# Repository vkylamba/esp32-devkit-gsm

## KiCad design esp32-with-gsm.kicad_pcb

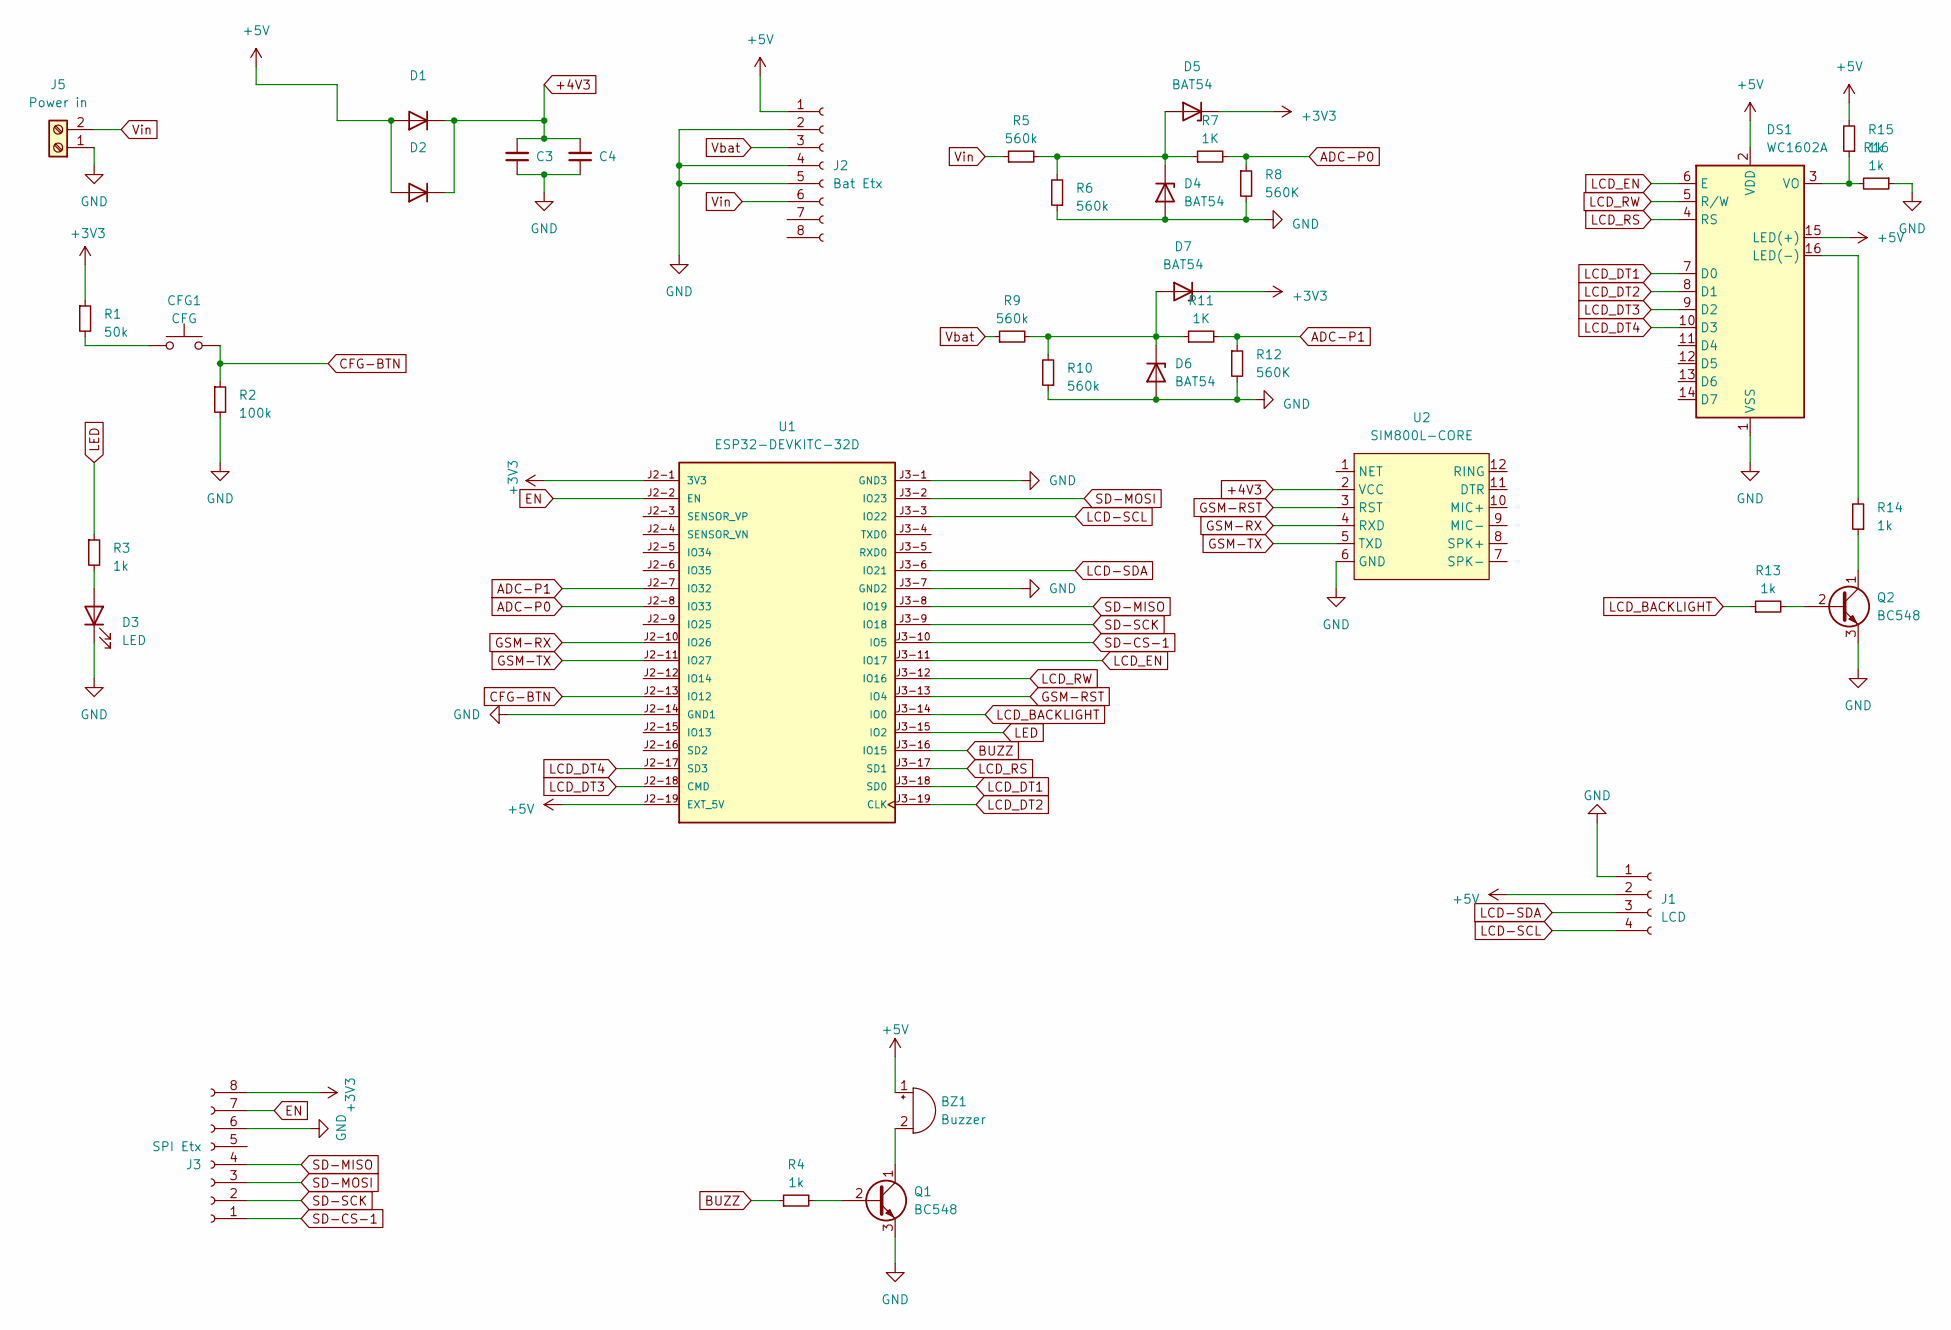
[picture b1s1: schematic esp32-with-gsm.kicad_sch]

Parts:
BZ1: Buzzer; Buzzer_12x9.5RM7.6
C3, C4: 470uF; C_Disc_D8.0mm_W2.5mm_P5.00mm
CFG1: CFG; PinHeader_1x02_P2.00mm_Vertical
D1, D2: 1N4007, SS14; D_0805_2012Metric
D3: LED; LED_D3.0mm_FlatTop
D4, D5, D6, D7: BAT54; D_0805_2012Metric
DS1: WC1602A
J1: LCD; PinHeader_1x04_P2.54mm_Vertical
J2: Bat Etx; PinHeader_1x08_P2.54mm_Vertical
J3: SPI Etx; PinHeader_1x08_P2.54mm_Vertical
J5: Power in; TerminalBlock_Altech_AK300-2_P5.00mm
Q1, Q2: BC548; TO-92_Inline
R1: 50k; R_0805_2012Metric
R2: 100k; R_0805_2012Metric
R3, R4, R13, R14, R15, R16: 1k; R_0805_2012Metric
R5, R6, R9, R10: 560k; R_0805_2012Metric
R7, R11: 1K; R_0805_2012Metric
R8, R12: 560K; R_0805_2012Metric
U1: ESP32-DEVKITC-32D; MODULE_ESP32-DEVKITC-32D; PARTREV V4
U2: SIM800L-CORE

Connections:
+3V3: D5.1 (K), D7.1 (K), J3.8, R1.1, U1.J2-1 (3V3)
+4V3: C3.2, C4.2, D1.1 (K), D2.1 (K), U2.2 (VCC)
+5V: BZ1.1 (+), D1.2 (A), D2.2 (A), DS1.2 (VDD), DS1.15 (LED(+)), J1.2, J2.1, R15.2, U1.J2-19 (EXT_5V)
ADC-P0: R7.2, R8.1, U1.J2-8 (IO33)
ADC-P1: R11.2, R12.1, U1.J2-7 (IO32)
BUZZ: R4.1, U1.J3-16 (IO15)
CFG-BTN: CFG1.2, R2.1, U1.J2-13 (IO12)
EN: J3.7, U1.J2-2 (EN)
GND: C3.1, C4.1, D3.1 (K), D4.2 (A), D6.2 (A), DS1.1 (VSS), J1.1, J2.2, J2.4, J2.5, J3.6, J5.1, Q1.3 (E), Q2.3 (E), R2.2, R6.1, R8.2, R10.1, R12.2, R16.1, U1.J2-14 (GND1), U1.J3-1 (GND3), U1.J3-7 (GND2), U2.6 (GND)
GSM-RST: U1.J3-13 (IO4), U2.3 (RST)
GSM-RX: U1.J2-10 (IO26), U2.4 (RXD)
GSM-TX: U1.J2-11 (IO27), U2.5 (TXD)
LCD-SCL: J1.4, U1.J3-3 (IO22)
LCD-SDA: J1.3, U1.J3-6 (IO21)
LCD_BACKLIGHT: R13.1, U1.J3-14 (IO0)
LCD_DT1: DS1.7 (D0), U1.J3-18 (SD0)
LCD_DT2: DS1.8 (D1), U1.J3-19 (CLK)
LCD_DT3: DS1.9 (D2), U1.J2-18 (CMD)
LCD_DT4: DS1.10 (D3), U1.J2-17 (SD3)
LCD_EN: DS1.6 (E), U1.J3-11 (IO17)
LCD_RS: DS1.4 (RS), U1.J3-17 (SD1)
LCD_RW: DS1.5 (R/W), U1.J3-12 (IO16)
LED: R3.1, U1.J3-15 (IO2)
unnamed: BZ1.2 (-), Q1.1 (C)
unnamed: CFG1.1, R1.2
unnamed: D3.2 (A), R3.2
unnamed: D4.1 (K), D5.2 (A), R5.2, R6.2, R7.1
unnamed: D6.1 (K), D7.2 (A), R9.2, R10.2, R11.1
unnamed: DS1.16 (LED(-)), R14.2
unnamed: DS1.3 (VO), R15.1, R16.2
unnamed: Q1.2 (B), R4.2
unnamed: Q2.2 (B), R13.2
unnamed: Q2.1 (C), R14.1
SD-CS-1: J3.1, U1.J3-10 (IO5)
SD-MISO: J3.4, U1.J3-8 (IO19)
SD-MOSI: J3.3, U1.J3-2 (IO23)
SD-SCK: J3.2, U1.J3-9 (IO18)
Vbat: J2.3, R9.1
Vin: J2.6, J5.2, R5.1

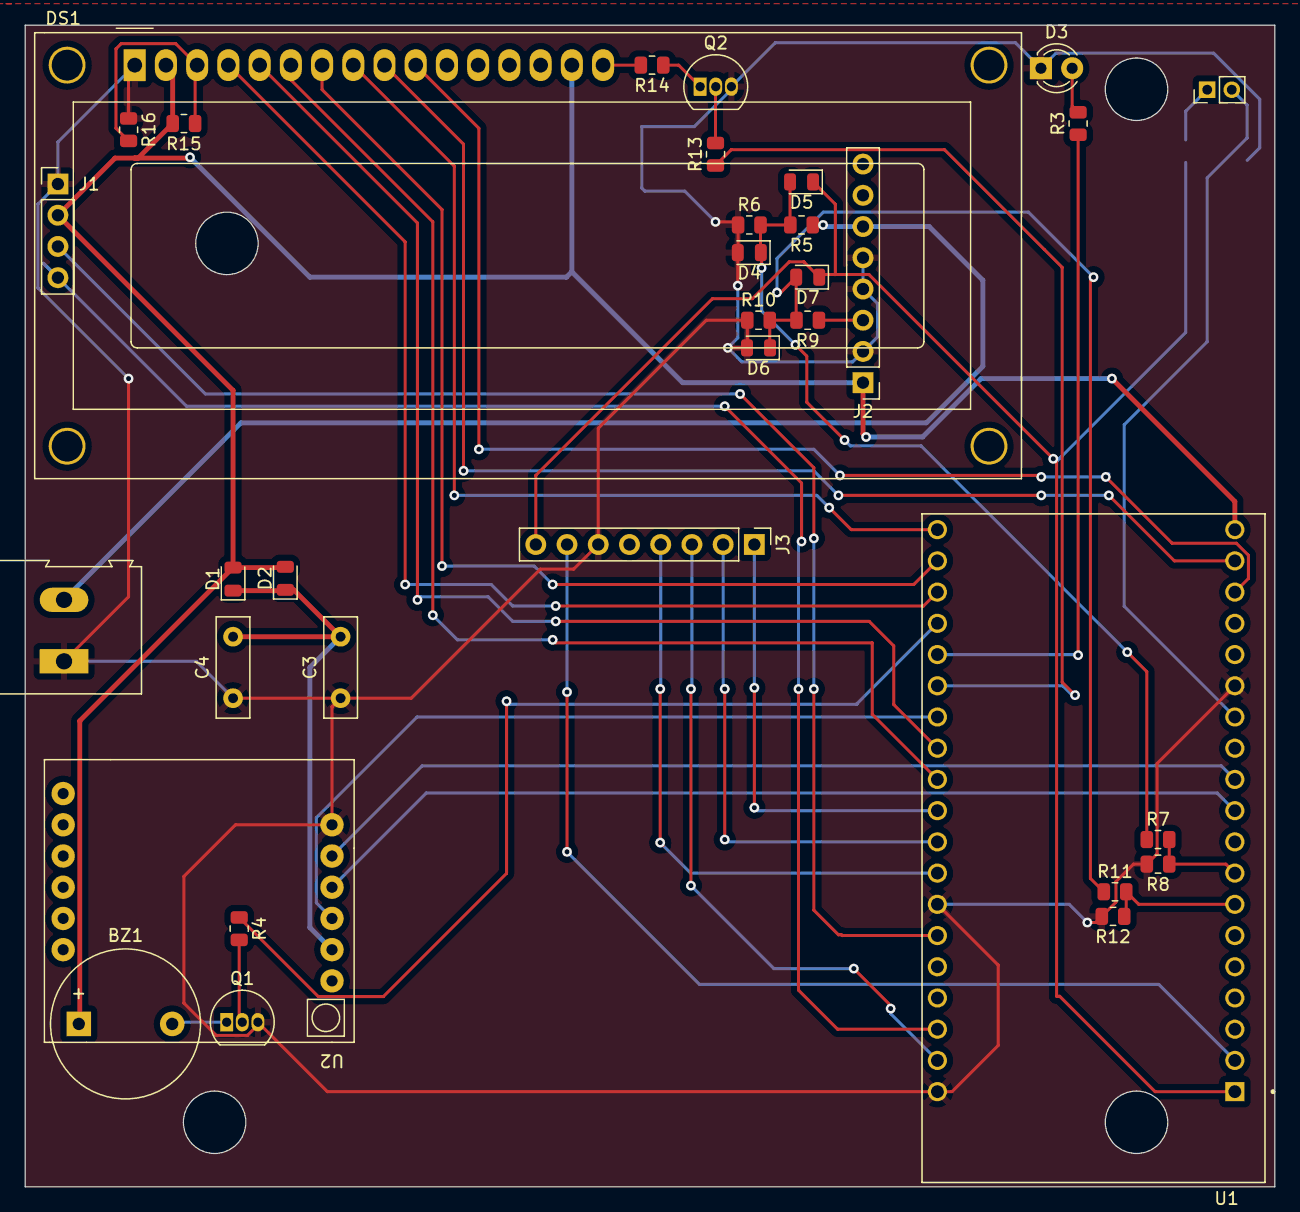
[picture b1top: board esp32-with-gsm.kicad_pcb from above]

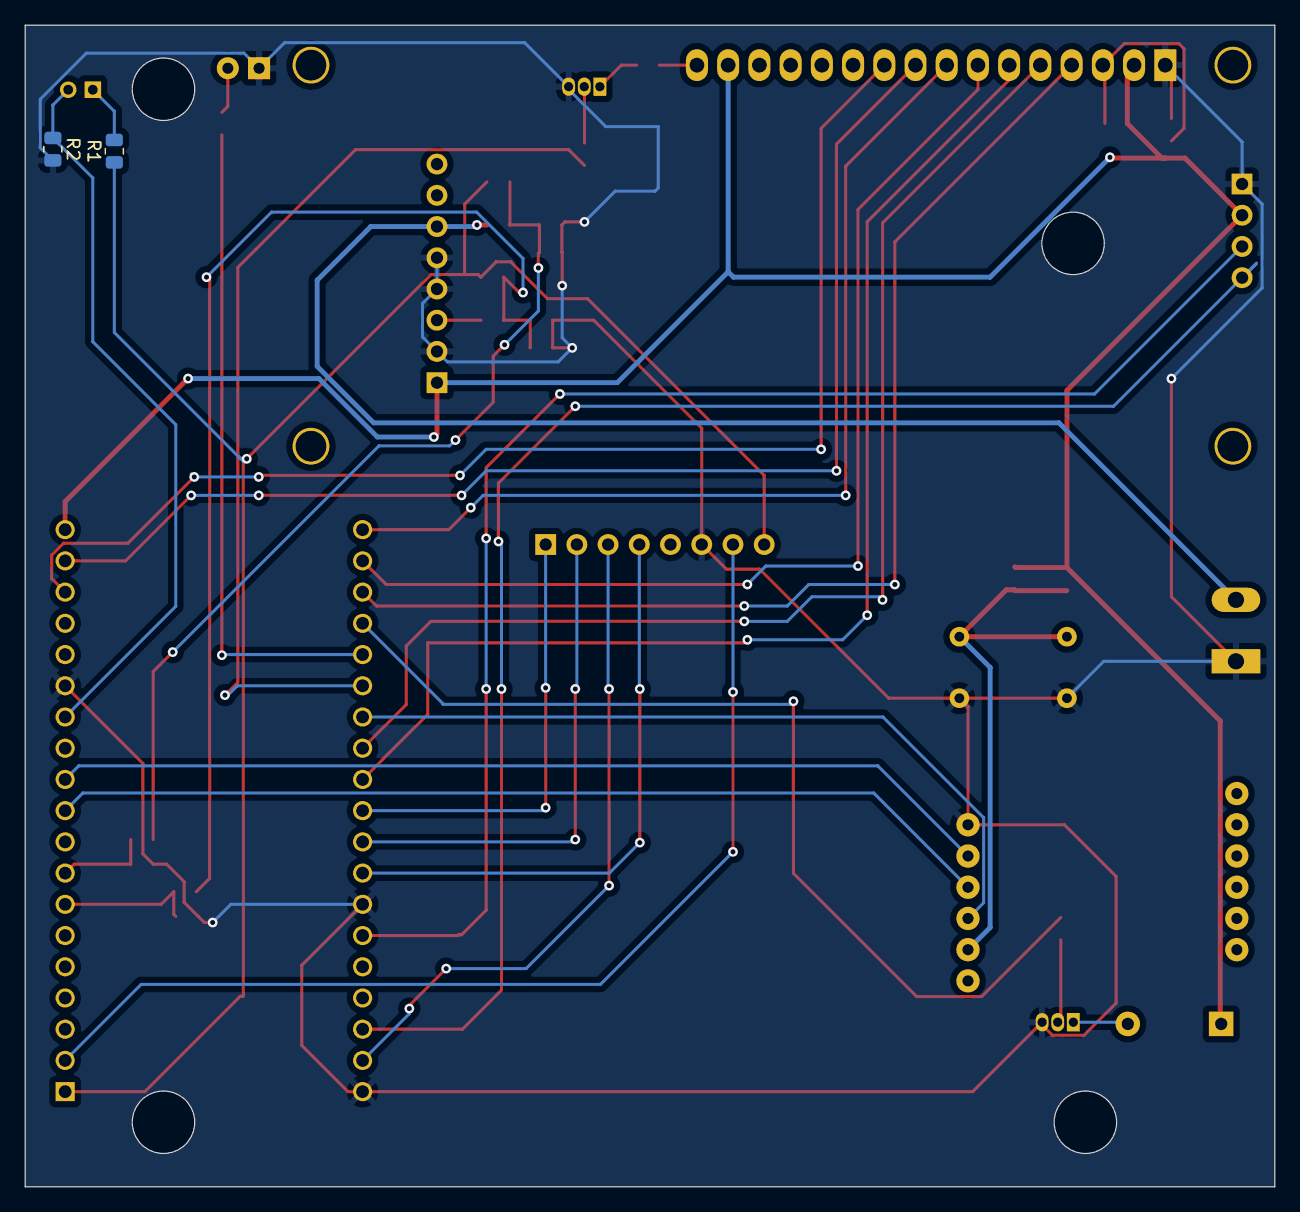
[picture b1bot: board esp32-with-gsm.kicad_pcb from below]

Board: 2 copper layers, 101.7 x 94.5 mm, 36 parts (2 on the bottom side), 39 nets.

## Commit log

2024-06-26 PCB ready
2024-11-16 updating circuit
2024-11-19 Added v2r1
